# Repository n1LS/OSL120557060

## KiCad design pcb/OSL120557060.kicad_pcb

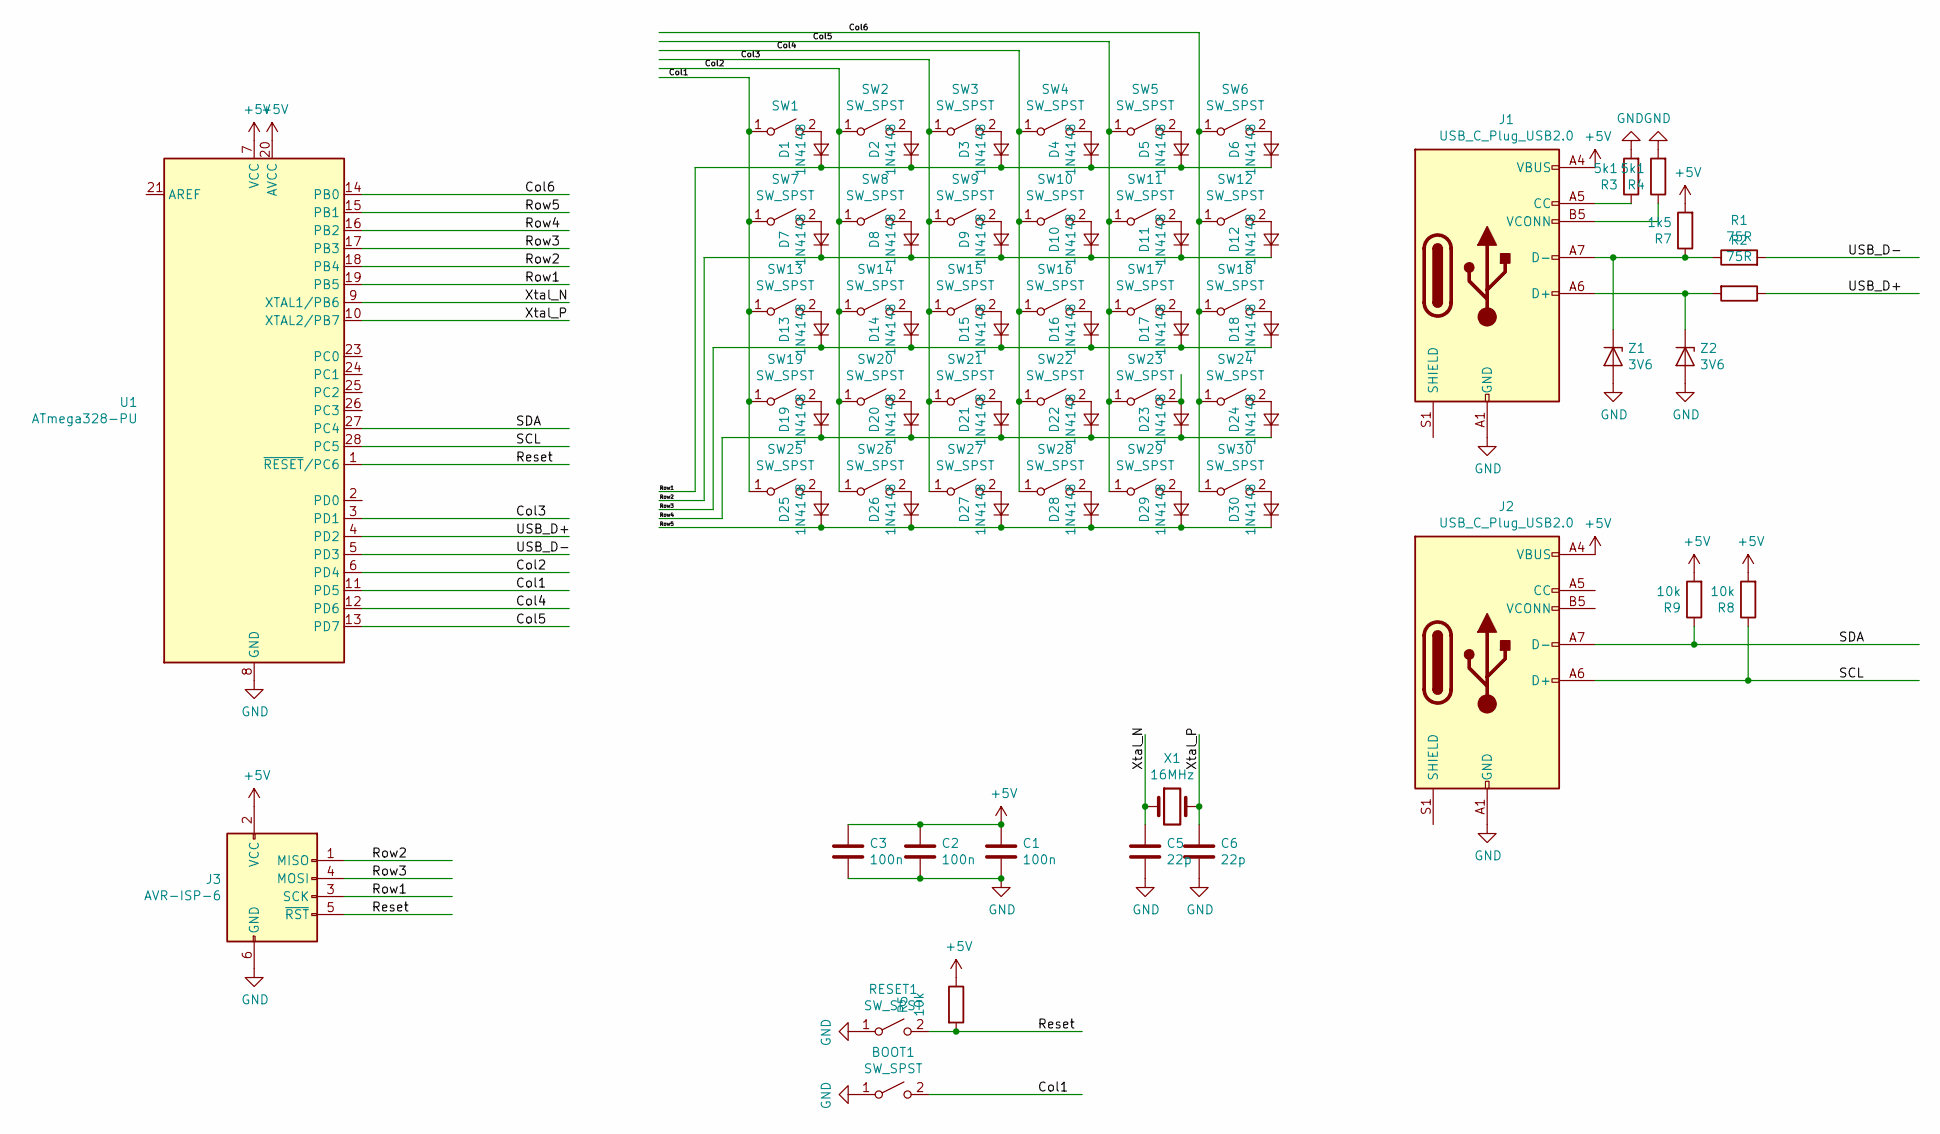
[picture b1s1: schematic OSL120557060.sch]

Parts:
BOOT1: SW_SPST; SW_SPST_B3U-1000P
C1, C2, C3: 100n; C_Disc_D3.0mm_W1.6mm_P2.50mm
C5, C6: 22p; C_Disc_D3.0mm_W1.6mm_P2.50mm
D1, D2, D3, D4, D5, D6, D7, D8, D9, D10, D11, D12, D13, D14, D15, D16, D17, D18, D19, D20, D21, D22, D23, D24, D25, D26, D27, D28, D29, D30: 1N4148; D_T-1_P5.08mm_Horizontal
J1, J2: USB_C_Plug_USB2.0; USB_C_Receptacle_GCT_USB4085
J3: AVR-ISP-6; PinHeader_2x03_P2.54mm_Vertical
R1, R2: 75R; R_Axial_DIN0207_L6.3mm_D2.5mm_P7.62mm_Horizontal
R3, R4: 5k1; R_Axial_DIN0207_L6.3mm_D2.5mm_P7.62mm_Horizontal
R5, R8, R9: 10k; R_Axial_DIN0207_L6.3mm_D2.5mm_P7.62mm_Horizontal
R7: 1k5; R_Axial_DIN0207_L6.3mm_D2.5mm_P7.62mm_Horizontal
RESET1: SW_SPST; SW_SPST_B3U-1000P
SW1, SW2, SW3, SW4, SW5, SW6, SW7, SW8, SW9, SW10, SW11, SW12, SW13, SW14, SW15, SW16, SW17, SW18, SW19, SW20, SW21, SW22, SW23, SW24, SW25, SW26, SW27, SW28, SW29, SW30: SW_SPST; SW_Cherry_MX_1.00u_Plate
U1: ATmega328-PU; DIP-28_W7.62mm
X1: 16MHz; Crystal_HC49-4H_Vertical
Z1, Z2: 3V6; D_T-1_P5.08mm_Horizontal

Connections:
+5V: C1.1, C2.1, C3.1, J1.A4 (VBUS), J1.A9 (VBUS), J1.B4 (VBUS), J1.B9 (VBUS), J2.A4 (VBUS), J2.A9 (VBUS), J2.B4 (VBUS), J2.B9 (VBUS), J3.2 (VCC), R5.1, R7.2, R8.2, R9.2, U1.7 (VCC), U1.20 (AVCC)
/Col1: BOOT1.2 (B), SW1.1 (A), SW7.1 (A), SW13.1 (A), SW19.1 (A), SW25.1 (A), U1.11 (PD5); also elsewhere on the board
/Col2: SW2.1 (A), SW8.1 (A), SW14.1 (A), SW20.1 (A), SW26.1 (A), U1.6 (PD4)
/Col3: SW3.1 (A), SW9.1 (A), SW15.1 (A), SW21.1 (A), SW27.1 (A), U1.3 (PD1)
/Col4: SW4.1 (A), SW10.1 (A), SW16.1 (A), SW22.1 (A), SW28.1 (A), U1.12 (PD6)
/Col5: SW5.1 (A), SW11.1 (A), SW17.1 (A), SW23.1 (A), SW29.1 (A), U1.13 (PD7)
/Col6: SW6.1 (A), SW12.1 (A), SW18.1 (A), SW24.1 (A), SW30.1 (A), U1.14 (PB0)
/Reset: J3.5 (~RST), R5.2, RESET1.2 (B), U1.1 (~RESET~/PC6); also elsewhere on the board
/Row1: D1.1 (K), D2.1 (K), D3.1 (K), D4.1 (K), D5.1 (K), D6.1 (K), J3.3 (SCK), U1.19 (PB5)
/Row2: D7.1 (K), D8.1 (K), D9.1 (K), D10.1 (K), D11.1 (K), D12.1 (K), J3.1 (MISO), U1.18 (PB4)
/Row3: D13.1 (K), D14.1 (K), D15.1 (K), D16.1 (K), D17.1 (K), D18.1 (K), J3.4 (MOSI), U1.17 (PB3)
/Row4: D19.1 (K), D20.1 (K), D21.1 (K), D22.1 (K), D23.1 (K), D24.1 (K), U1.16 (PB2)
/Row5: D25.1 (K), D26.1 (K), D27.1 (K), D28.1 (K), D29.1 (K), D30.1 (K), U1.15 (PB1)
/SCL: J2.A6 (D+), R8.1, U1.28 (PC5)
/SDA: J2.A7 (D-), R9.1, U1.27 (PC4)
/USB_D+: R2.1, U1.4 (PD2)
/USB_D-: R1.2, U1.5 (PD3)
/Xtal_N: C5.1, U1.9 (XTAL1/PB6), X1.1
/Xtal_P: C6.1, U1.10 (XTAL2/PB7), X1.2
GND: BOOT1.1 (A), C1.2, C2.2, C3.2, C5.2, C6.2, J1.A1 (GND), J1.A12 (GND), J1.B1 (GND), J1.B12 (GND), J2.A1 (GND), J2.A12 (GND), J2.B1 (GND), J2.B12 (GND), J3.6 (GND), R3.2, R4.2, RESET1.1 (A), U1.8 (GND), U1.22 (GND), Z1.2 (A), Z2.2 (A); also elsewhere on the board
unnamed: D1.2 (A), SW1.2 (B)
unnamed: D2.2 (A), SW2.2 (B)
unnamed: D3.2 (A), SW3.2 (B)
unnamed: D4.2 (A), SW4.2 (B)
unnamed: D5.2 (A), SW5.2 (B)
unnamed: D6.2 (A), SW6.2 (B)
unnamed: D7.2 (A), SW7.2 (B)
unnamed: D8.2 (A), SW8.2 (B)
unnamed: D9.2 (A), SW9.2 (B)
unnamed: D10.2 (A), SW10.2 (B)
unnamed: D11.2 (A), SW11.2 (B)
unnamed: D12.2 (A), SW12.2 (B)
unnamed: D13.2 (A), SW13.2 (B)
unnamed: D14.2 (A), SW14.2 (B)
unnamed: D15.2 (A), SW15.2 (B)
unnamed: D16.2 (A), SW16.2 (B)
unnamed: D17.2 (A), SW17.2 (B)
unnamed: D18.2 (A), SW18.2 (B)
unnamed: D19.2 (A), SW19.2 (B)
unnamed: D20.2 (A), SW20.2 (B)
unnamed: D21.2 (A), SW21.2 (B)
unnamed: D22.2 (A), SW22.2 (B)
unnamed: D23.2 (A), SW23.2 (B)
unnamed: D24.2 (A), SW24.2 (B)
unnamed: D25.2 (A), SW25.2 (B)
unnamed: D26.2 (A), SW26.2 (B)
unnamed: D27.2 (A), SW27.2 (B)
unnamed: D28.2 (A), SW28.2 (B)
unnamed: D29.2 (A), SW29.2 (B)
unnamed: D30.2 (A), SW30.2 (B)
unnamed: J1.A5 (CC), R3.1
unnamed: J1.A6 (D+), R2.2, Z2.1 (K)
unnamed: J1.A7 (D-), R1.1, R7.1, Z1.1 (K)
unnamed: J1.B5 (VCONN), R4.1

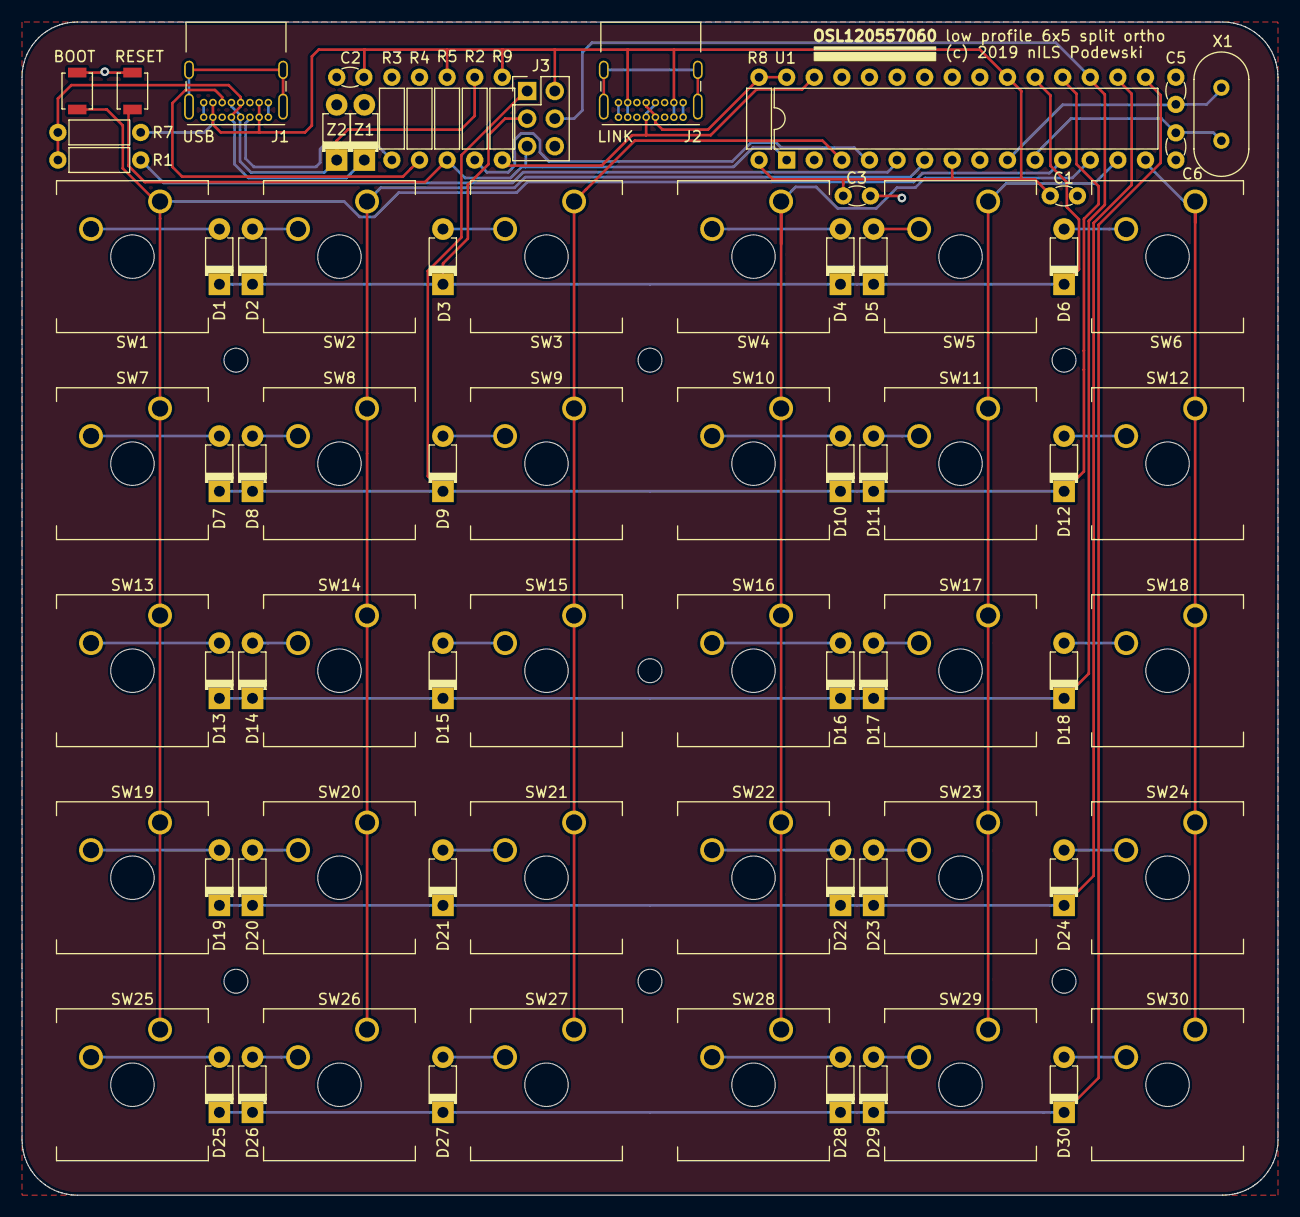
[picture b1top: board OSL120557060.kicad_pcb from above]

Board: 2 copper layers, 115.6 x 108.0 mm, 82 parts (0 on the bottom side), 54 nets.

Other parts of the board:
BOOT: SW_SPST; SW_SPST_B3U-1000P
RESET: SW_SPST; SW_SPST_B3U-1000P

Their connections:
/Col1: BOOT.2; also elsewhere on the board
/Reset: RESET.2; also elsewhere on the board
GND: BOOT.1, RESET.1; also elsewhere on the board

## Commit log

2019-06-20 added missing reset switch
2019-06-20 updated schematic with reset switch
2019-06-21 added smaller reset switches moved components to allow for all around plate
2019-06-21 changed component footprints
2019-06-24 * added plate pcb * fixed reset button placement
2019-06-24 * added missing zener diodes on the usb port
2019-06-27 moved from micro usb to usb-c (yw wilba)
2019-07-08 * added mount pis to pcb * improved plate layout
2019-07-08 * updated cache lib
2019-07-09 * added pulldown resistors to allow usb-c usb-c cables * fixed usb-c footprint for reversibility
2019-07-10 silkscreen updates
2019-07-12 - added first revision BOM - improved base layout for plates

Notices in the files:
pcb/OSL120557060.kicad_pcb:
(c) 2019 nILS Podewski
